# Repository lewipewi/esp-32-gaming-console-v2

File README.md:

# Emulator Console v2

A handheld Game Boy (DMG) emulator console built around an **ESP32-S3**, designed from scratch in KiCad. The target game is Pokémon Red/Blue.

v2 is a ground-up redesign of the first board (v1, "Rev A"). v1 never booted, and the redesign fixes everything that went wrong with it. Every part on v2 came from parts already on hand. Nothing new was bought for this revision.

---

## At a glance

| | |
|---|---|
| MCU | ESP32-S3-WROOM-1U-N8R8 (dual-core 240 MHz, 8 MB flash, 8 MB octal PSRAM). WiFi unused |
| Display | 2.4" 320×240 IPS, ST7789, SPI at 80 MHz, landscape |
| Storage | microSD, 1-bit SDMMC, with card detect |
| Audio | MAX98357A I²S class-D amp → 8 Ω 1 W speaker |
| Controls | D-pad, A, B, Select, Start, L, R (10 buttons), plus RESET and BOOT |
| Power | 1-cell Li-ion with built-in protection, USB-C charging at 500 mA, play-while-charging |
| Board | 70 × 95 mm, 4-layer, 1.6 mm, JLC04161H-7628 stackup |
| Debug | Native USB (Serial/JTAG), UART header, labelled test points, rail-OK LEDs |

---

## How v2 differs from v1

### Why there's a v2

The v1 board never powered up properly:

- It **never enumerated over USB**, and plugging it into a laptop **crashed the laptop**.
- The buck-boost regulator **ran hot on battery alone**.
- With the board unpowered, **+3V3 measured 0.4 Ω to GND**. That's a dead short on the main rail.

There was no way to isolate the fault. v1 had no test points, no debug UART, and the only regulator was a fine-pitch VSON package. Inspection also found heavy uncleaned flux, loose solder balls and a solder bridge on the module.

Debugging it also exposed several design-level problems: no audio on battery, no power path, and a write-only display bus. So rather than patch v1, v2 started from a blank schematic.

### Change summary

| Area | v1 (Rev A) | v2 | Why |
|---|---|---|---|
| **3.3 V regulation** | TPS63020 buck-boost, VSON-14 | **Two AP2112K-3.3 LDOs**: one for the MCU, one for peripherals | A buck-boost only recovers the last ~5% of a Li-ion cell's capacity. Two LDOs are simpler, have no switching layout to get wrong, are easy to hand-solder and rework, and each one stays under ~150 mA |
| **Power path** | Battery → switch → system | **USB-priority load sharing** (SS24 + AO3401) | The system runs from USB while the cell charges undisturbed. **The board runs from USB with no battery fitted** |
| **Power switch** | Slide switch carried the full battery current | **Slide switch drives both LDO enable pins** | The switch (rated ~0.5 A) now carries microamps |
| **Charge current** | 1 A | **500 mA** (2 × 1.2 kΩ PROG) | Stays inside a default USB 2.0 port budget, and the TP4056 runs cooler |
| **Amp supply** | `+5V_USB`: **no audio on battery** | `VSYS` | Audio works on battery |
| **Amp control** | Always on, 9 dB gain, (L+R)/2 mode via 1 MΩ | **Enabled by GPIO46** through 1 kΩ (left-channel mode), **6 dB gain** | No pop at boot and no idle current. Lower gain protects the 1 W speaker. Firmware sends mono audio |
| **Display bus** | SPI on arbitrary pins, write-only | **SPI2 dedicated pins** (SCK IO12, MOSI IO11) + **FMARK** | Reliable 80 MHz, which is the emulator's frame-time bottleneck. FMARK enables tear-free updates |
| **Display mounting** | Flat footprint | **Landscape, flex wrapped around the board edge** to pads on the back (custom footprint) | The screen is centred on the front, and all other parts live on the back |
| **Backlight** | Anode straight to 3.3 V, no current limit | **Series resistor R23** + low-side FET with PWM | The LED forward voltage is as low as 2.8 V. Without a resistor, current depends on the panel batch |
| **microSD** | 4-bit SDMMC, no card detect | **1-bit SDMMC + card detect** | 1-bit mode loads a 1 MB ROM in under half a second and frees 3 GPIOs |
| **Buttons** | 8 | **10** (adds L/R shoulders on the back) | Menu and save-state shortcuts without button chords |
| **Battery sense** | None | **÷2 divider (1 MΩ/1 MΩ + 100 nF) → IO16** | Battery gauge and low-battery shutdown |
| **Charge status** | CHRG/STDBY tied to GND | **CHRG → IO9** with a 10 kΩ pull-up to 3.3 V | Firmware can show a charging icon |
| **Speaker** | JST PH header (the speaker plug is actually 1.25 mm pitch) | **Solder pads with strain relief** | The original connector never fitted |
| **Debug** | USB only | **UART header, labelled test points, rail-OK LEDs** | There's always a way in, and faults can be found by probing |
| **PCB** | Rectangular, Select/Start on the left edge, no mounting holes | **4-layer, 70 × 95 mm**, centred controls, 4 × M2 holes | Solid ground plane, better ergonomics, ready for an enclosure |

---

## Hardware

### Power

```
USB-C ── USBLC6 ESD ── D+/D− ─────────────────────────── ESP32-S3 (IO19/IO20)
  │
+5V_VBUS ──┬──► TP4056 (500 mA) ──► VBAT ──► AO3401 (on when no USB) ──┐
           │                                                           │
           └──► SS24 ───────────────────────────────────────────────────┴──► VSYS (3.0–4.6 V)
                                                                              │
                         ┌──────────────────────────┬─────────────────────────┤
                AP2112K → +3V3_MCU          AP2112K → +3V3_PERIPHERAL     MAX98357A
               (EN ← slide switch)          (EN ← slide switch)
                   ESP32-S3                   display, backlight, microSD
```

- **On USB:** the SS24 feeds VSYS, the AO3401 is held off (its gate is on VBUS), and the TP4056 charges the cell independently.
- **On battery:** a 10 kΩ resistor pulls the AO3401 gate low, so the cell feeds VSYS through about 50 mΩ.
- **Switch off:** both LDOs shut down. The amp sits in shutdown because GPIO46 is low. Total drain is a few µA.
- **Charging works with the switch off.**
- **Low-battery protection:** the cell's own protection circuit plus a firmware cutoff. The LDOs drop out gracefully, so the board stays usable down to about 3.0 V.

### Boot and strap pins

| Pin | How it's handled |
|---|---|
| EN | 10 kΩ pull-up + 1 µF (~10 ms delay), RESET button, test point |
| IO0 | 10 kΩ pull-up, BOOT button, test point |
| IO45 | 10 kΩ pull-down, which selects 3.3 V VDD_SPI for the N8R8. It also drives the backlight gate, so the screen stays dark until firmware lights it |
| IO46 | Held low at reset by the amp's internal 100 kΩ pull-down through the 1 kΩ |
| IO3 | Test point only; its strap function is inactive unless an eFuse is burned |
| IO35–37 | Left unconnected (used inside the module by the octal PSRAM) |

**Flashing:** over USB-C. If USB doesn't enumerate, connect a USB-UART adapter to the header (`3V3 GND TX RX`), hold **BOOT**, tap **RESET**.

### GPIO map

| GPIO | Function | | GPIO | Function |
|---|---|---|---|---|
| 0 | BOOT (strap) | | 21 | TFT FMARK |
| 1 | R shoulder | | 38 | B |
| 2 | Select | | 39 | A |
| 3 | Test point | | 40 | I²S DIN |
| 4 | Up | | 41 | I²S BCLK |
| 5 | SD card detect | | 42 | I²S LRCLK |
| 6 | SD DAT0 | | 43 | UART TX (header) |
| 7 | SD CLK | | 44 | UART RX (header) |
| 8 | Right | | 45 | Backlight PWM (strap, pulled down) |
| 9 | CHRG (charging = low) | | 46 | Amp enable (SD_MODE) |
| 10 | TFT DC | | 47 | Start |
| 11 | TFT MOSI (SPI2 dedicated pin) | | 48 | L shoulder |
| 12 | TFT SCK (SPI2 dedicated pin) | | 19 / 20 | USB D− / D+ |
| 13 | TFT CS | | 35–37 | Octal PSRAM (do not use) |
| 14 | TFT RST | | | |
| 15 | SD CMD | | | |
| 16 | VBAT sense (ADC2; WiFi stays off) | | | |
| 17 | Down | | | |
| 18 | Left | | | |

Buttons short to GND and use the internal pull-ups, with debouncing in firmware.

### PCB

- **Stackup:** F.Cu (front, mostly buttons) / In1 power areas (VBUS, VSYS, +3V3_MCU, +3V3_PERIPHERAL) / In2 solid GND / B.Cu (main routing).
  - The back layer, where almost everything is routed, sits right over the solid ground plane.
- **Front:** display and the 8 face buttons only.
  - Nothing through-hole sits behind the glass, so the front stays flat.
- **Back:** everything else. The module sits behind the screen, with power at the bottom by USB-C and audio in the bottom right.
- **USB:** D+/D− are length-matched (52.1 mm each), 0.2 mm wide with a 0.25 mm gap. That calculates to about 105–113 Ω differential. It's above the 90 Ω target, but that doesn't matter at full-speed USB (12 Mbps).
- **Other layout details:**
  - GND stitching vias around the edge and through open areas, plus teardrops.
  - Thermal vias under the TP4056, the amp and the module's ground pad.
  - Vias are covered by solder mask (tented).

### Display flex

The panel's flex can't twist, so it wraps around the board's **side edge** to solder pads on the back. A custom footprint places the glass centred on its anchor, with the 16 pads on B.Cu at the calculated fold position. The pads are 5 mm long, which absorbs tolerance in the flex height.

**Important:** don't use KiCad's *Flip* on this footprint. A fold around the edge doesn't mirror the pin order, but Flip would.

---

## Bring-up order

Each stage adds one subsystem, so a fault points at whatever was just added.

0. **Harvest parts from v1.** The module, LCD, amp, slide switch and speaker are quantity 1 and come off the old board. Measure the bare module's 3V3 pin to GND first: a high reading means it's good; about 0.4 Ω means it's dead.
1. **Power only.** Check every rail for shorts before applying power. Then:
   - **USB with no battery:** VSYS ≈ 4.6 V, both rails at 3.3 V, both rail LEDs lit.
   - **Switch off:** the rails go to 0.
   - **Battery connected:** charging works.
   - **Unplug USB:** VSYS follows the battery.
2. **MCU.** It should enumerate as *USB JTAG/serial debug unit*. Run the rail, button and battery tests.
3. **Display.** Fill the screen, then step SPI from 40 to 80 MHz.
4. **microSD.** Mount the card; test card detect.
5. **Audio.** Test **on battery, with USB unplugged**. That was v1's main defect.

---

## Firmware notes

ESP-IDF v5.5. Key `sdkconfig` settings:

```
CONFIG_SPIRAM=y
CONFIG_SPIRAM_MODE_OCT=y
CONFIG_SPIRAM_SPEED_80M=y
CONFIG_ESPTOOLPY_FLASHSIZE_8MB=y
CONFIG_ESP_CONSOLE_USB_SERIAL_JTAG=y
```

- **Display:** SPI2 host, ST7789 with INVON (0x21). Rotate the image for landscape. Sync frame transfers to FMARK.
- **SD:** SDMMC with `slot_config.width = 1` (CLK 7 / CMD 15 / D0 6), plus card detect on IO5.
- **Audio:**
  - Drive IO46 high before starting I²S and low after stopping it.
  - Use `I2S_SLOT_MODE_MONO`; the amp runs in left-channel mode.
  - **Cap the volume.** On USB, VSYS is 4.6 V, which can push more than 1 W into the speaker.
- **Battery:** read IO16, ×2 for the cell voltage. Sample no faster than every few hundred ms. Save and power down below about 3.4 V.
- **Planned:** USB mass-storage mode, so ROMs can be copied over USB-C without opening the case. The microSD slot sits inside the enclosure.

---

## Known limitations

- **WiFi is not supported.** Transmit peaks (350–500 mA) would overload the MCU's LDO.
- **The microSD card is only reachable with the case open** until USB mass-storage mode is implemented.
- **Several parts are quantity 1**, harvested from v1: the ESP32-S3 module, LCD, MAX98357A, slide switch and speaker. A second fully populated board would need new ones.

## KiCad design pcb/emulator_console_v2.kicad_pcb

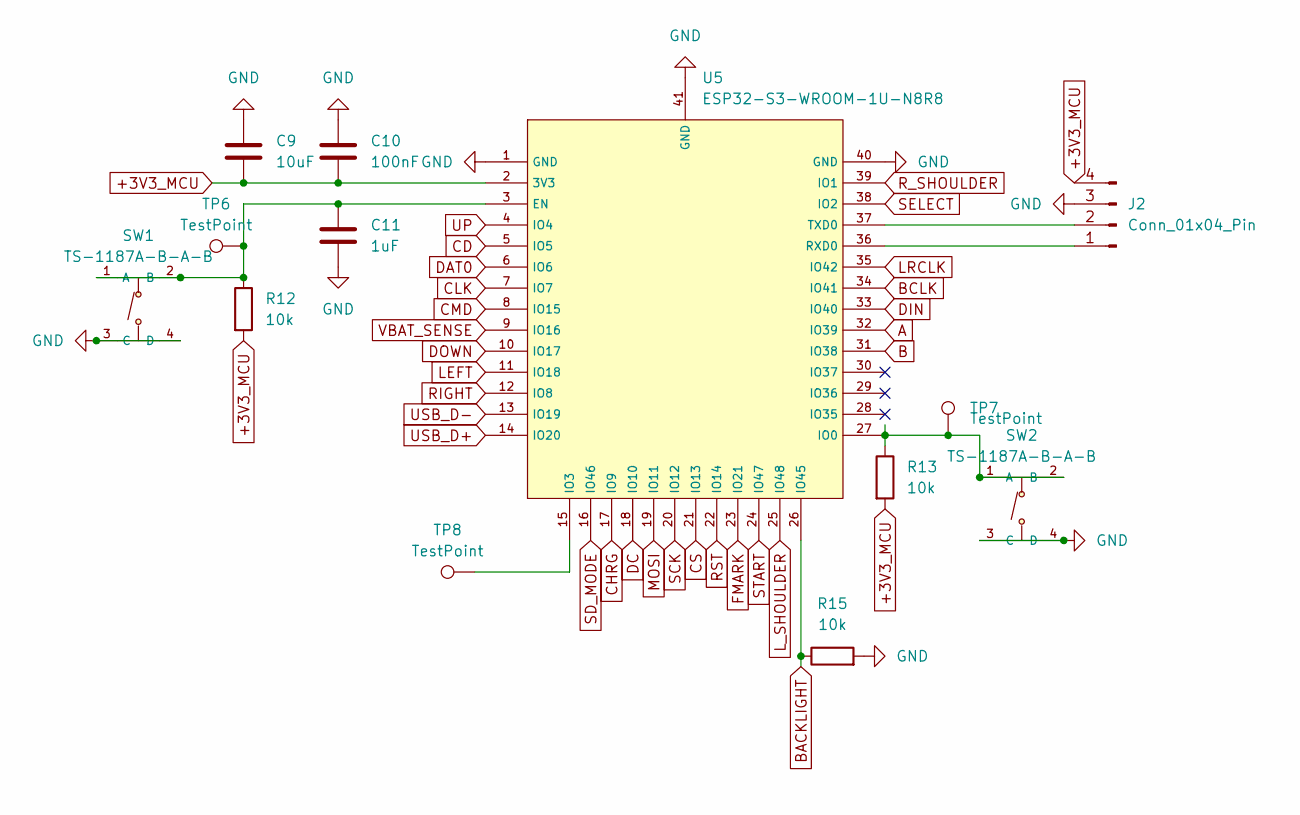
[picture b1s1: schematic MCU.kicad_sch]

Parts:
C9: 10uF; C_0805_2012Metric_Pad1.18x1.45mm_HandSolder
C10: 100nF; C_0603_1608Metric_Pad1.08x0.95mm_HandSolder
C11: 1uF; C_0603_1608Metric_Pad1.08x0.95mm_HandSolder
J2: Conn_01x04_Pin; PinHeader_1x04_P2.54mm_Vertical
R12, R13, R15: 10k; R_0603_1608Metric_Pad0.98x0.95mm_HandSolder
SW1, SW2: TS-1187A-B-A-B; C318884_SW-SMD_4P-L5_1-W5_1-P3_70-LS6_5-TL_H1_5; LCSC C318884
TP6, TP7, TP8: TestPoint; TestPoint_Pad_2.0x2.0mm
U5: ESP32-S3-WROOM-1U-N8R8; C2980300_WIRELM-SMD_ESP32-S3-WROOM-1U; LCSC C2980300

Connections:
+3V3_MCU: C9.2, C10.2, J2.4, R12.2, R13.2, U5.2 (3V3); also elsewhere on the board
A: U5.32 (IO39); also elsewhere on the board
B: U5.31 (IO38); also elsewhere on the board
BACKLIGHT: R15.1, U5.26 (IO45); also elsewhere on the board
BCLK: U5.34 (IO41); also elsewhere on the board
CD: U5.5 (IO5); also elsewhere on the board
CHRG: U5.17 (IO9); also elsewhere on the board
CLK: U5.7 (IO7); also elsewhere on the board
CMD: U5.8 (IO15); also elsewhere on the board
CS: U5.21 (IO13); also elsewhere on the board
DAT0: U5.6 (IO6); also elsewhere on the board
DC: U5.18 (IO10); also elsewhere on the board
DIN: U5.33 (IO40); also elsewhere on the board
DOWN: U5.10 (IO17); also elsewhere on the board
FMARK: U5.23 (IO21); also elsewhere on the board
GND: C9.1, C10.1, C11.2, J2.3, R15.2, SW1.3 (C), SW1.4 (D), SW2.3 (C), SW2.4 (D), U5.1 (GND), U5.40 (GND), U5.41 (GND); also elsewhere on the board
LEFT: U5.11 (IO18); also elsewhere on the board
LRCLK: U5.35 (IO42); also elsewhere on the board
L_SHOULDER: U5.25 (IO48); also elsewhere on the board
MOSI: U5.19 (IO11); also elsewhere on the board
unnamed: J2.1, U5.36 (RXD0)
unnamed: J2.2, U5.37 (TXD0)
unnamed: C11.1, R12.1, SW1.1 (A), SW1.2 (B), TP6.1 (1_1), U5.3 (EN)
unnamed: R13.1, SW2.1 (A), SW2.2 (B), TP7.1 (1_1), U5.27 (IO0)
unnamed: TP8.1 (1_1), U5.15 (IO3)
RIGHT: U5.12 (IO8); also elsewhere on the board
RST: U5.22 (IO14); also elsewhere on the board
R_SHOULDER: U5.39 (IO1); also elsewhere on the board
SCK: U5.20 (IO12); also elsewhere on the board
SD_MODE: U5.16 (IO46); also elsewhere on the board
SELECT: U5.38 (IO2); also elsewhere on the board
START: U5.24 (IO47); also elsewhere on the board
UP: U5.4 (IO4); also elsewhere on the board
USB_D+: U5.14 (IO20); also elsewhere on the board
USB_D-: U5.13 (IO19); also elsewhere on the board
VBAT_SENSE: U5.9 (IO16); also elsewhere on the board

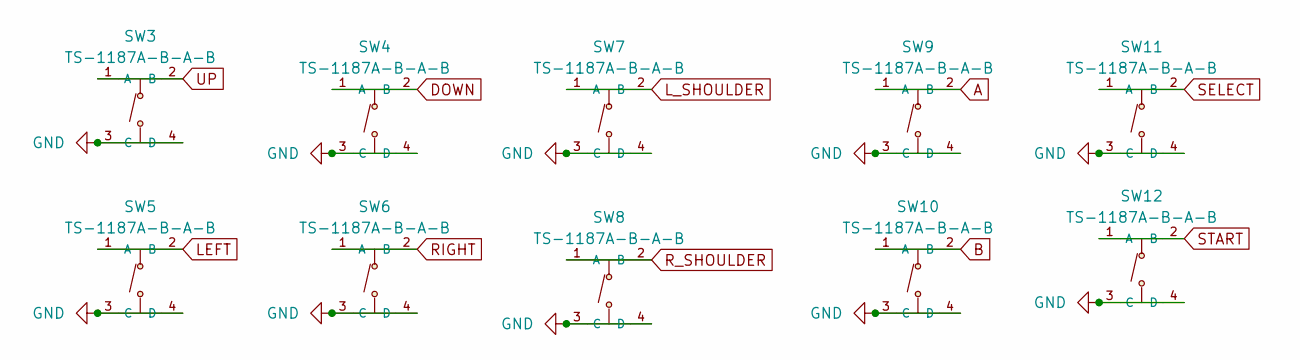
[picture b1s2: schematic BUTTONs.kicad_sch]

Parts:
SW3, SW4, SW5, SW6, SW7, SW8, SW9, SW10, SW11, SW12: TS-1187A-B-A-B; C318884_SW-SMD_4P-L5_1-W5_1-P3_70-LS6_5-TL_H1_5; LCSC C318884

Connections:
A: SW9.1 (A), SW9.2 (B); also elsewhere on the board
B: SW10.1 (A), SW10.2 (B); also elsewhere on the board
DOWN: SW4.1 (A), SW4.2 (B); also elsewhere on the board
GND: SW3.3 (C), SW3.4 (D), SW4.3 (C), SW4.4 (D), SW5.3 (C), SW5.4 (D), SW6.3 (C), SW6.4 (D), SW7.3 (C), SW7.4 (D), SW8.3 (C), SW8.4 (D), SW9.3 (C), SW9.4 (D), SW10.3 (C), SW10.4 (D), SW11.3 (C), SW11.4 (D), SW12.3 (C), SW12.4 (D); also elsewhere on the board
LEFT: SW5.1 (A), SW5.2 (B); also elsewhere on the board
L_SHOULDER: SW7.1 (A), SW7.2 (B); also elsewhere on the board
RIGHT: SW6.1 (A), SW6.2 (B); also elsewhere on the board
R_SHOULDER: SW8.1 (A), SW8.2 (B); also elsewhere on the board
SELECT: SW11.1 (A), SW11.2 (B); also elsewhere on the board
START: SW12.1 (A), SW12.2 (B); also elsewhere on the board
UP: SW3.1 (A), SW3.2 (B); also elsewhere on the board

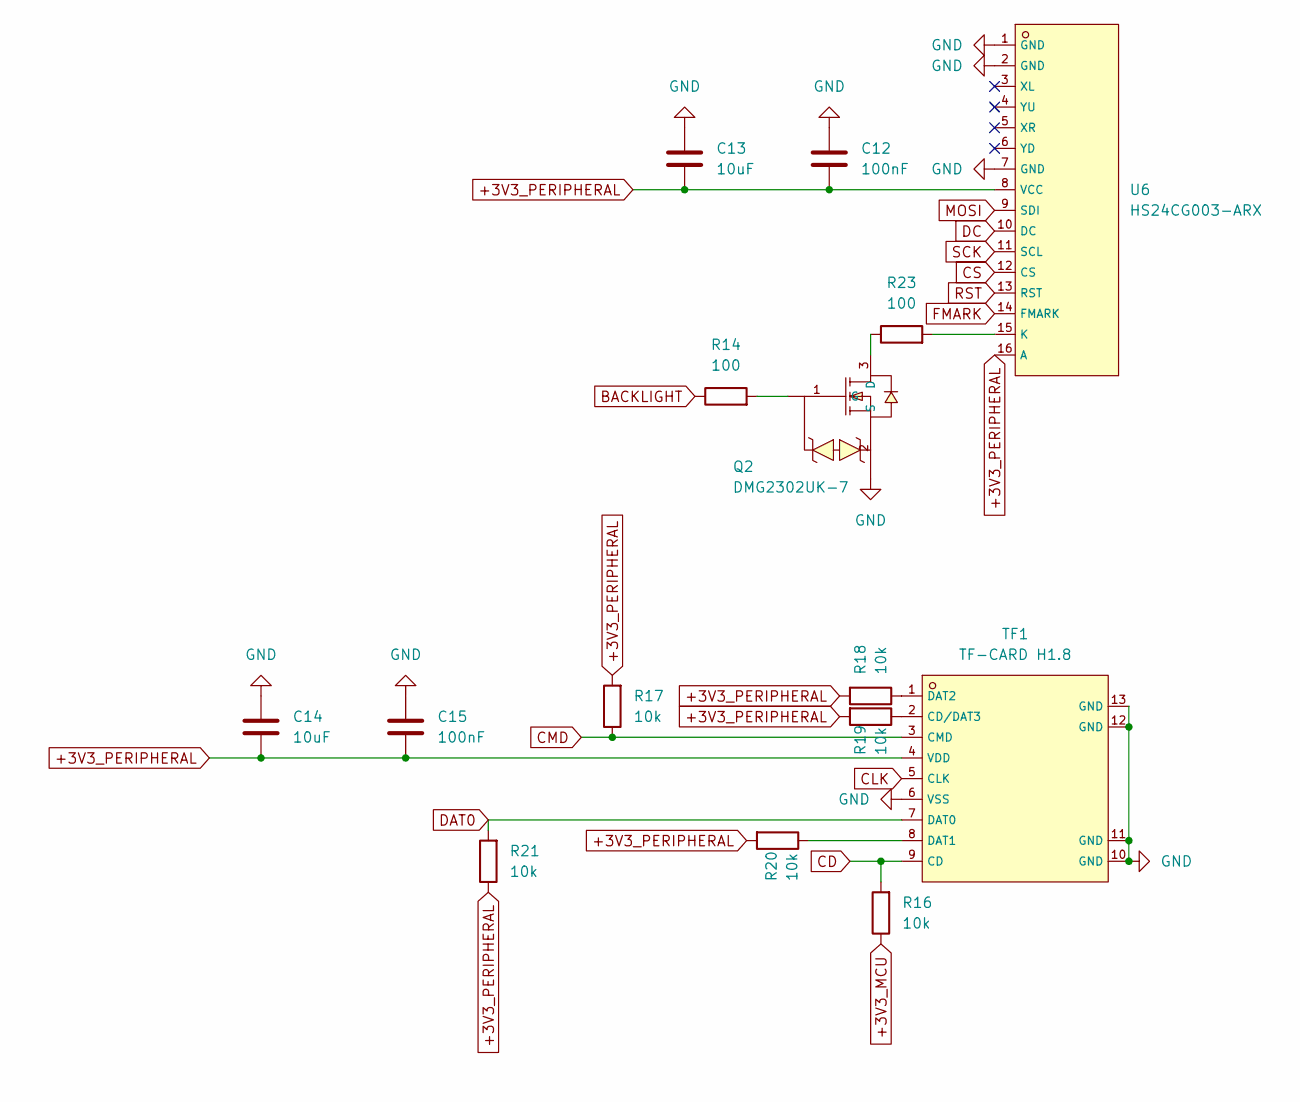
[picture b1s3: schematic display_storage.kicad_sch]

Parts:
C12, C15: 100nF; C_0603_1608Metric_Pad1.08x0.95mm_HandSolder
C13, C14: 10uF; C_0805_2012Metric_Pad1.18x1.45mm_HandSolder
Q2: DMG2302UK-7; C460977_SOT-23-3_L2_9-W1_3-P1_90-LS2_4-BR; LCSC C460977
R14, R23: 100; R_0603_1608Metric_Pad0.98x0.95mm_HandSolder
R16, R17, R18, R19, R20, R21: 10k; R_0603_1608Metric_Pad0.98x0.95mm_HandSolder
TF1: TF-CARD H1.8; C7529389_TF-SMD_TF-CARD-H1_8; LCSC C7529389
U6: HS24CG003-ARX; HS24CG003_SideWrap_W70; LCSC C5329583

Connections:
+3V3_MCU: R16.1; also elsewhere on the board
+3V3_PERIPHERAL: C12.2, C13.2, C14.2, C15.2, R17.2, R18.2, R19.2, R20.2, R21.1, TF1.4 (VDD), U6.8 (VCC), U6.16 (A); also elsewhere on the board
BACKLIGHT: R14.1; also elsewhere on the board
CD: R16.2, TF1.9 (CD); also elsewhere on the board
CLK: TF1.5 (CLK); also elsewhere on the board
CMD: R17.1, TF1.3 (CMD); also elsewhere on the board
CS: U6.12 (CS); also elsewhere on the board
DAT0: R21.2, TF1.7 (DAT0); also elsewhere on the board
DC: U6.10 (DC); also elsewhere on the board
FMARK: U6.14 (FMARK); also elsewhere on the board
GND: C12.1, C13.1, C14.1, C15.1, Q2.2 (S), TF1.6 (VSS), TF1.10 (GND), TF1.11 (GND), TF1.12 (GND), TF1.13 (GND), U6.1 (GND), U6.2 (GND), U6.7 (GND); also elsewhere on the board
MOSI: U6.9 (SDI); also elsewhere on the board
unnamed: Q2.3 (D), R23.1
unnamed: Q2.1 (G), R14.2
unnamed: R19.1, TF1.2 (CD/DAT3)
unnamed: R20.1, TF1.8 (DAT1)
unnamed: R18.1, TF1.1 (DAT2)
unnamed: R23.2, U6.15 (K)
RST: U6.13 (RST); also elsewhere on the board
SCK: U6.11 (SCL); also elsewhere on the board

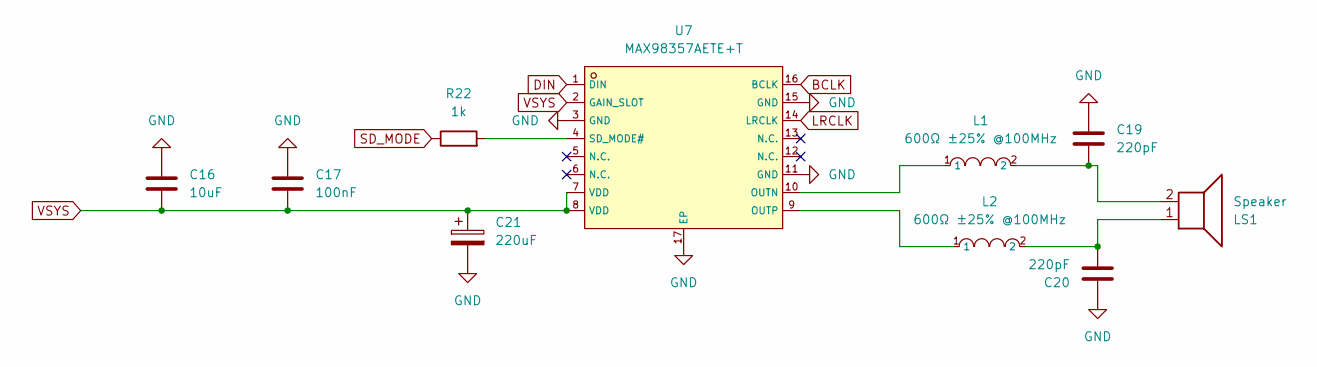
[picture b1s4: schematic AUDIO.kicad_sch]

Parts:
C16: 10uF; C_0805_2012Metric_Pad1.18x1.45mm_HandSolder
C17: 100nF; C_0603_1608Metric_Pad1.08x0.95mm_HandSolder
C19, C20: 220pF; C_0603_1608Metric_Pad1.08x0.95mm_HandSolder
C21: 220uF; CP_Radial_D6.3mm_P2.50mm
L1, L2: 600Ω ±25% @100MHz; C21519_L0805; LCSC C21519
LS1: Speaker; SolderWire-0.15sqmm_1x02_P4mm_D0.5mm_OD1.5mm_Relief
R22: 1k; R_0603_1608Metric_Pad0.98x0.95mm_HandSolder
U7: MAX98357AETE+T; C910544_TQFN-16_L3_0-W3_0-P0_50-BL-EP1_5; LCSC C910544

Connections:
BCLK: U7.16 (BCLK); also elsewhere on the board
DIN: U7.1 (DIN); also elsewhere on the board
GND: C16.1, C17.1, C19.1, C20.1, C21.2, U7.3 (GND), U7.11 (GND), U7.15 (GND), U7.17 (EP); also elsewhere on the board
LRCLK: U7.14 (LRCLK); also elsewhere on the board
unnamed: C19.2, L1.2, LS1.2
unnamed: C20.2, L2.2, LS1.1
unnamed: L1.1, U7.10 (OUTN)
unnamed: L2.1, U7.9 (OUTP)
unnamed: R22.2, U7.4 (SD_MODE#)
SD_MODE: R22.1; also elsewhere on the board
VSYS: C16.2, C17.2, C21.1, U7.2 (GAIN_SLOT), U7.7 (VDD), U7.8 (VDD); also elsewhere on the board

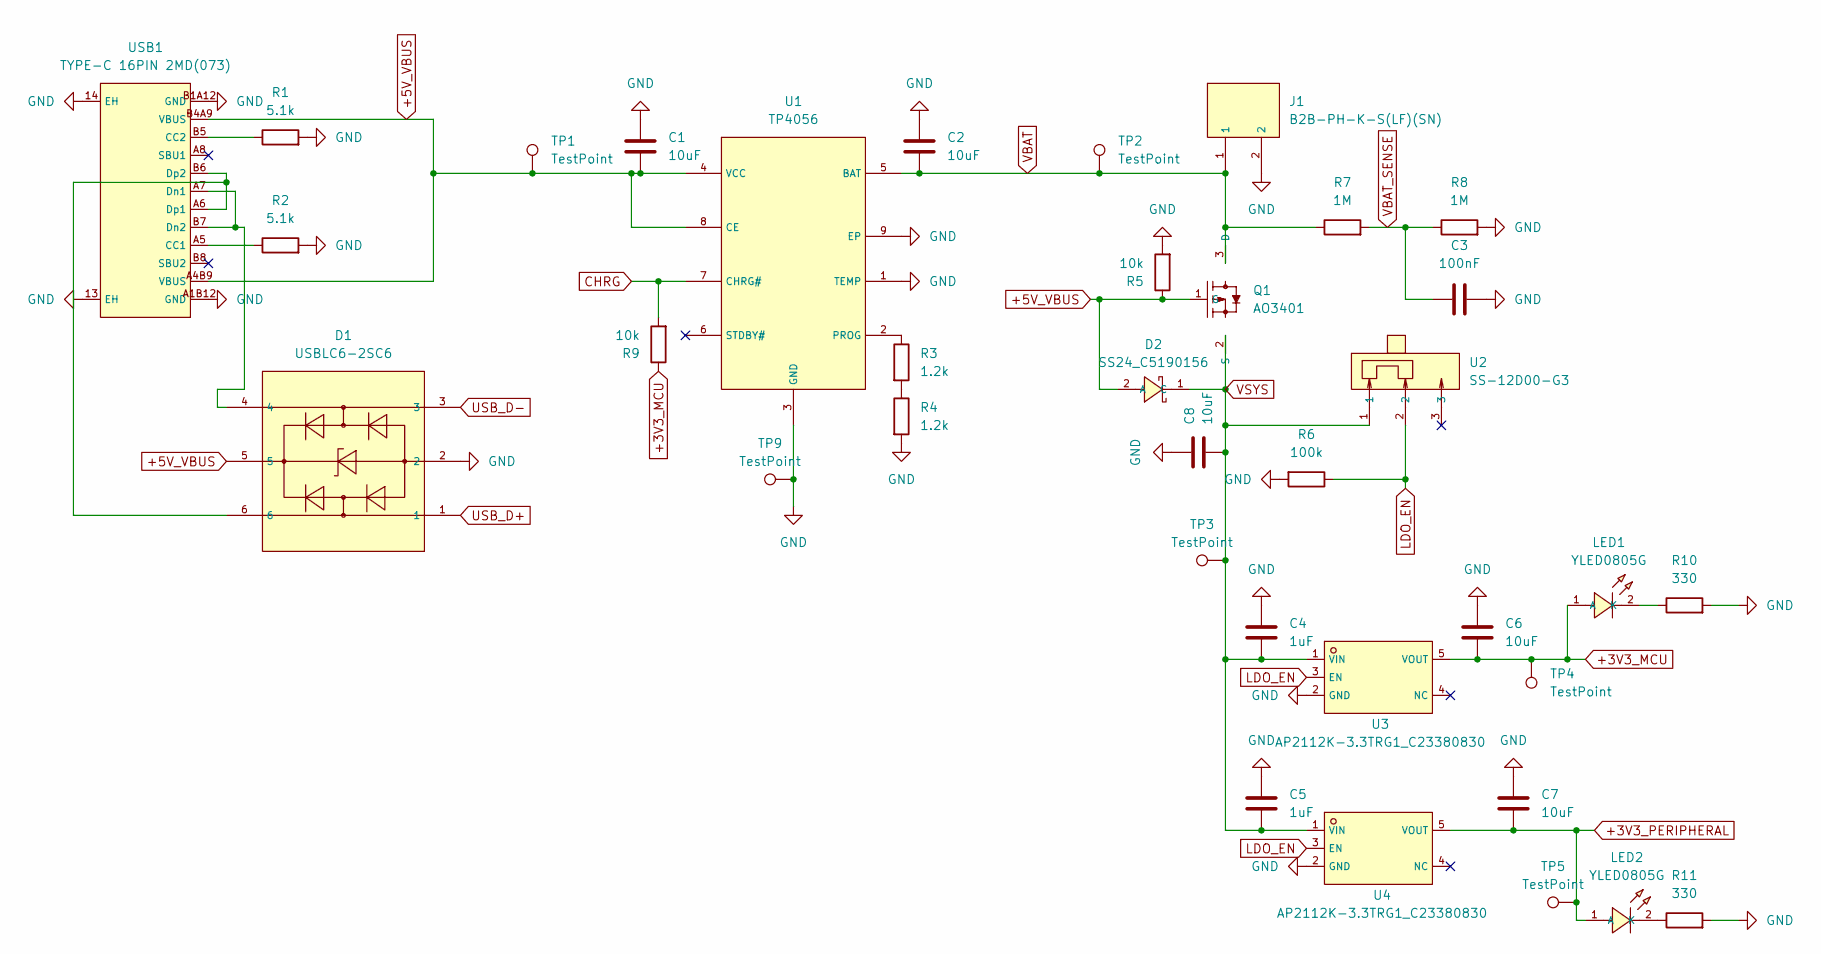
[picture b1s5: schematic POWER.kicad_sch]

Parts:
C1, C2, C6, C7, C8: 10uF; C_0805_2012Metric_Pad1.18x1.45mm_HandSolder
C3: 100nF; C_0603_1608Metric_Pad1.08x0.95mm_HandSolder
C4, C5: 1uF; C_0603_1608Metric_Pad1.08x0.95mm_HandSolder
D1: USBLC6-2SC6; C7519_SOT-23-6_L2_9-W1_6-P0_95-LS2_8-BL; LCSC C7519
D2: SS24_C5190156; C5190156_SMB_L4_3-W3_6-LS5_4-RD; LCSC C5190156
J1: B2B-PH-K-S(LF)(SN); C131337_CONN-TH_B2B-PH-K-S; LCSC C131337
LED1, LED2: YLED0805G; C25170728_LED0805-FD-GREEN; LCSC C25170728
Q1: AO3401; C181091_SOT-23-3_L2_9-W1_3-P1_90-LS2_4-BR; LCSC C181091
R1, R2: 5.1k; R_0603_1608Metric_Pad0.98x0.95mm_HandSolder
R3, R4: 1.2k; R_0603_1608Metric_Pad0.98x0.95mm_HandSolder
R5, R9: 10k; R_0603_1608Metric_Pad0.98x0.95mm_HandSolder
R6: 100k; R_0603_1608Metric_Pad0.98x0.95mm_HandSolder
R7, R8: 1M; R_0603_1608Metric_Pad0.98x0.95mm_HandSolder
R10, R11: 330; R_0603_1608Metric_Pad0.98x0.95mm_HandSolder
TP1, TP2, TP3, TP4, TP5, TP9: TestPoint; TestPoint_Pad_2.0x2.0mm
U1: TP4056; C16581_ESOP-8_L4_9-W3_9-P1_27-LS6_0-BL-EP; LCSC C16581
U2: SS-12D00-G3; C22355741_SW-TH_3P-L8_8-W3_9-P2_50_SS12D00G3; LCSC C22355741
U3, U4: AP2112K-3.3TRG1_C23380830; C23380830_SOT-23-5_L2_9-W1_6-P0_95-LS2_8-BR; LCSC C23380830
USB1: TYPE-C 16PIN 2MD(073); C2765186_USB-C-SMD_TYPE-C-16PIN-2MD-073; LCSC C2765186

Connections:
+3V3_MCU: C6.2, LED1.1 (A), R9.1, TP4.1 (1_1), U3.5 (VOUT); also elsewhere on the board
+3V3_PERIPHERAL: C7.2, LED2.1 (A), TP5.1 (1_1), U4.5 (VOUT); also elsewhere on the board
+5V_VBUS: C1.2, D1.5, D2.2 (A), Q1.1 (G), R5.1, TP1.1 (1_1), U1.4 (VCC), U1.8 (CE), USB1.A4B9 (VBUS), USB1.B4A9 (VBUS)
CHRG: R9.2, U1.7 (CHRG#); also elsewhere on the board
GND: C1.1, C2.1, C3.2, C4.1, C5.1, C6.1, C7.1, C8.1, D1.2, J1.2, R1.2, R2.2, R4.2, R5.2, R6.2, R8.2, R10.2, R11.2, TP9.1 (1_1), U1.1 (TEMP), U1.3 (GND), U1.9 (EP), U3.2 (GND), U4.2 (GND), USB1.13 (EH), USB1.14 (EH), USB1.A1B12 (GND), USB1.B1A12 (GND); also elsewhere on the board
LDO_EN: R6.1, U2.2, U3.3 (EN), U4.3 (EN)
unnamed: LED1.2 (K), R10.1
unnamed: LED2.2 (K), R11.1
unnamed: R3.2, R4.1
unnamed: R3.1, U1.2 (PROG)
unnamed: R2.1, USB1.A5 (CC1)
unnamed: R1.1, USB1.B5 (CC2)
unnamed: D1.4, USB1.A7 (Dn1), USB1.B7 (Dn2)
unnamed: D1.6, USB1.A6 (Dp1), USB1.B6 (Dp2)
USB_D+: D1.1; also elsewhere on the board
USB_D-: D1.3; also elsewhere on the board
VBAT: C2.2, J1.1, Q1.3 (D), R7.1, TP2.1 (1_1), U1.5 (BAT)
VBAT_SENSE: C3.1, R7.2, R8.1; also elsewhere on the board
VSYS: C4.2, C5.2, C8.2, D2.1 (C), Q1.2 (S), TP3.1 (1_1), U2.1, U3.1 (VIN), U4.1 (VIN); also elsewhere on the board

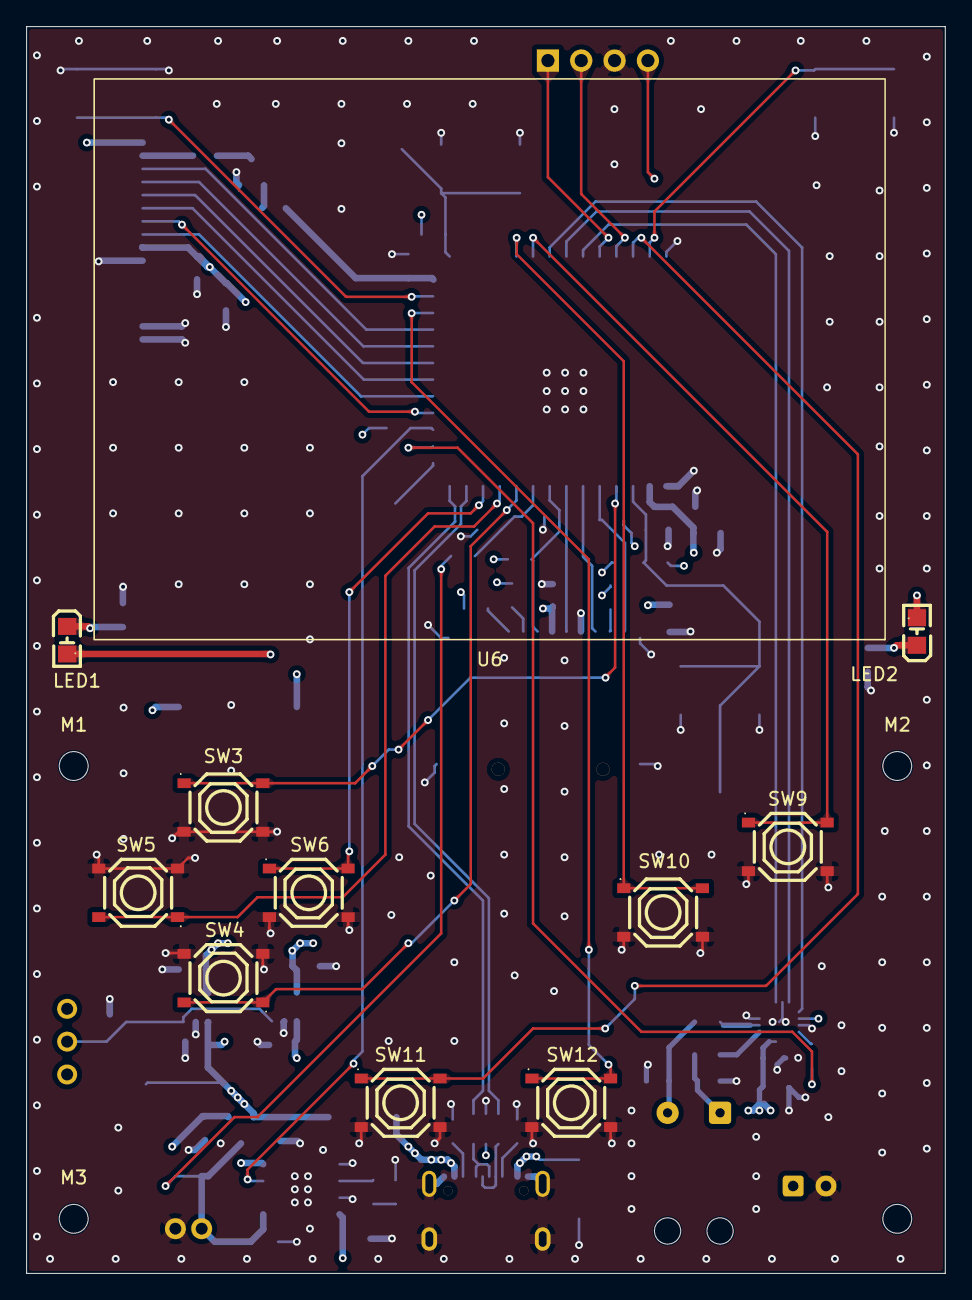
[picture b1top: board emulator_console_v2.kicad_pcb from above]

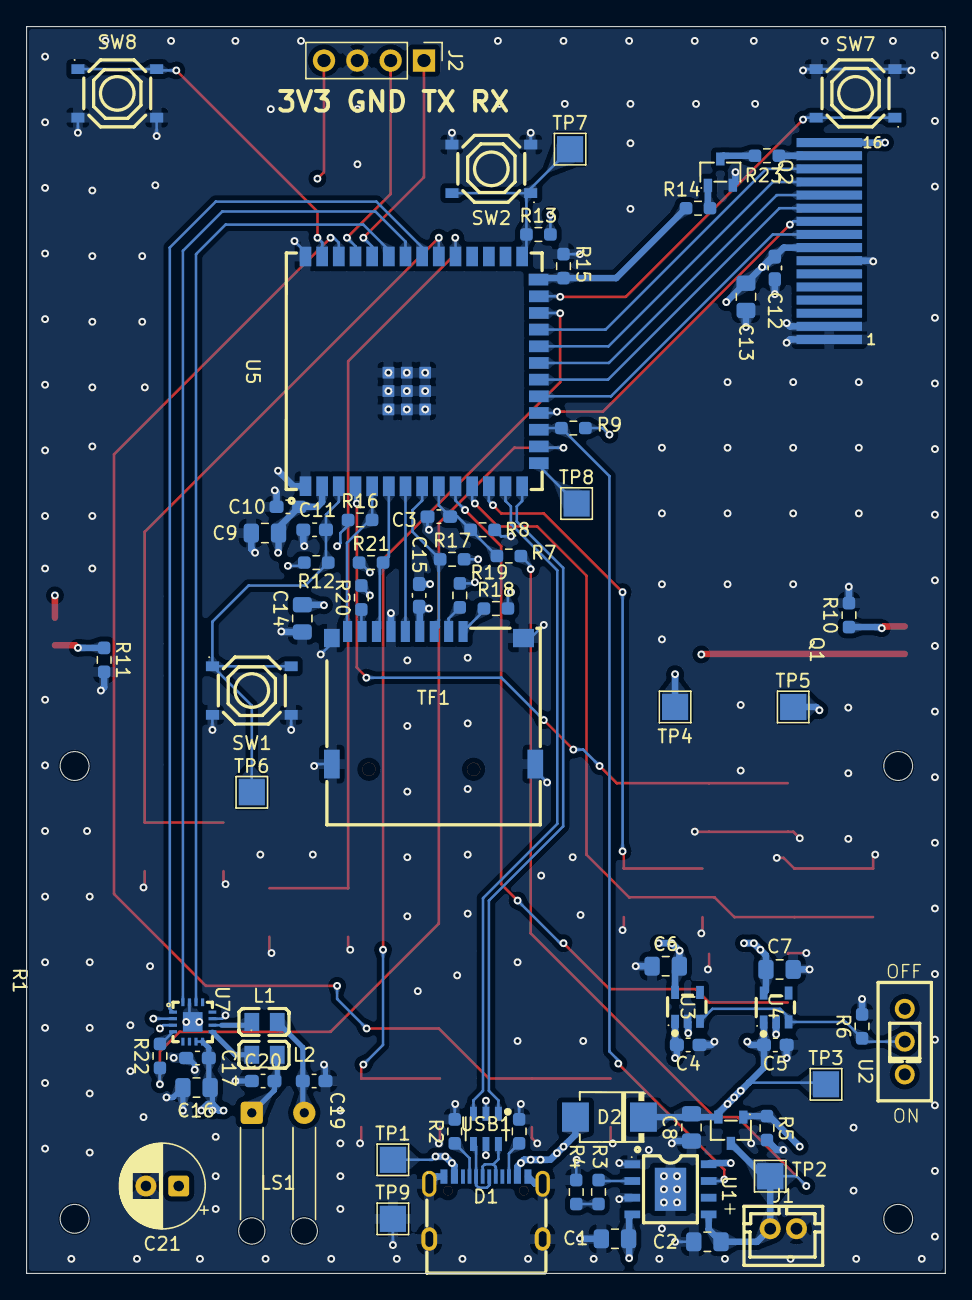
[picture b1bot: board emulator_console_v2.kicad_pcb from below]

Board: 4 copper layers, 70.0 x 95.0 mm, 88 parts (73 on the bottom side), 60 nets.

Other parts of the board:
M1, M2, M3, M4: MountingHole_2.2mm_M2
